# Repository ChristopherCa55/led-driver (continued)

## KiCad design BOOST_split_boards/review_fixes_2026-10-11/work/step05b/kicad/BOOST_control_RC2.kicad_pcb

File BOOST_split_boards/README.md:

# BOOST LED driver — two-board split, routed (KiCad 10)

## Current state (2026-09-25): start here

**The release package is `FINAL_2026-09-25/`** (scenario A: 5 bare PCBs of each board, 2 complete sets assembled
by JLCPCB). Start with `FINAL_2026-09-25/README.md` and its `7_docs/ORDER_CHECKLIST.md`.

**Schematic rev6 is in `BOOST-github/BOOST/BOOST.kicad_sch`** (written 2026-09-25 on the user's OK).
- Rev5 is backed up in `previous/2026-09-25/schematic_rev5/`.
- ERC 0/0, the same report as rev5; netlist `BOOST_9-25_rev6.net`.
- Netdiff: six values only. Parity 0 on both boards. DRC 0 errors, 0 unconnected.
- Nothing is open before ordering; follow `fab_2026-09-24/ORDER_CHECKLIST.md`.

The re-designed boards are not the `BOOST_power.kicad_pcb` / `BOOST_control.kicad_pcb` in this folder. Those are the
older routing described below, kept as shipped. The current boards (working copies keep `_NOT_FOR_FAB`; the release
copies are in `FINAL_2026-09-25/2_boards/`):

| | Board | Status |
|---|---|---|
| Power | `route_2026-09-16/BOOST_power_route_v19_NOT_FOR_FAB.kicad_pcb` | **release (RC2)**: v18 + rev6 values |
| Power | `route_2026-09-16/BOOST_power_route_v18_NOT_FOR_FAB.kicad_pcb` | v17 + via moves + J10 1.05 mm (approved 2026-09-24) |
| Power | `route_2026-09-16/BOOST_power_route_v17_NOT_FOR_FAB.kicad_pcb` | frozen v16 + MOSFET orientation silk |
| Card | `card_route_2026-09-22/BOOST_control_route_c3b_NOT_FOR_FAB.kicad_pcb` | **release (RC2)**: c3 + J11 1.05 mm |
| Card | `card_route_2026-09-22/BOOST_control_route_c3_NOT_FOR_FAB.kicad_pcb` | accepted 2026-09-24 |

- Fabrication + assembly package: `fab_2026-09-24/README.md` (RC2), `COST_SUMMARY.md`, `ORDER_CHECKLIST.md`.
- Assembly pack: `BUILD_NOTES.md` and `case_drilling_2026-09-15/` (rev B).
- 3D model and clearances: `assembly_3d_2026-09-24/` (rebuilt 2026-09-25 with the chosen hardware).
- M1 turn-off re-check with the routed loop: `sim_m1_2026-09-24/README.md` (accepted 2026-09-25).
- `BOOST_power.kicad_pro` carries netclass priorities (2026-09-24; backup in `previous/2026-09-24/`).

The rest of this file describes the older routing and is kept for reference.

| file | what |
|---|---|
| `BOOST_power.kicad_pcb` + `.kicad_pro` | 74 × 86 mm, 8 layers, 121 footprints |
| `BOOST_control.kicad_pcb` + `.kicad_pro` | 60 × 60 mm, 8 layers, 154 footprints |
| `DRC_power.rpt`, `DRC_control.rpt` | KiCad 10 DRC, run on these exact files |
| `power_routed.png`, `control_routed.png` | layer-coloured plots |
| `previous/` | the boards as they were before this pass |

Keep the `.kicad_pro` beside each board — it carries the net classes, and without
it DRC falls back to defaults and reports differently.

## Final state, measured by KiCad 10 DRC on the delivered files

| | POWER | CONTROL |
|---|---|---|
| unconnected **pads** | **0** | **0** |
| unconnected items (zone fill) | 2 | **0** |
| clearance | **0** | **0** |
| shorting items | **0** | **0** |
| hole-to-hole / hole clearance | **0** | **0** |
| solder-mask bridges | **0** | **0** |
| silkscreen | **0** | **0** |
| isolated copper | **0** | **0** |
| dangling track/via | 1 | **0** |
| library warning | 1 | 0 |
| track segments / vias / zones | 4630 / 305 / 16 | 3061 / 357 / 4 |

Every pad-to-pad connection on both boards is routed. The two remaining items on
the power board are between two *zones* — a fragment of the F.Cu ground pour that
does not reach the B.Cu ground pour across the surface. Both boards keep solid
ground planes on In1 and In6 with hundreds of stitching vias, so those fragments
are grounded through the stack; the ratsnest line is KiCad noting that no surface
copper joins them directly.

The `lib_footprint_issues` warning says the footprint library `CSCF3218-6R8MC`
(the inductor L1) is not in your footprint library table. The footprint itself is
embedded in the board and is correct — this is about your library configuration,
not the layout, and it goes away once that library is registered.

## Stackup (8 layers, both boards)

```
F.Cu    components, signal, high-current pours (2 oz)
In1.Cu  solid GND plane        <- no tracks, verified 0
In2.Cu  signal
In3.Cu  signal
In4.Cu  5V plane + signal
In5.Cu  signal
In6.Cu  solid GND plane        <- no tracks, verified 0
B.Cu    components, gate drive, signal (2 oz)
```

## Net classes (in the .kicad_pro, enforced by DRC)

| class | track | clearance | via | nets |
|---|---|---|---|---|
| Power | 2.0 mm | 0.25 mm | 0.8/0.4 | Vin, rsense_lo, LX, m2/3/4_source, Vout_1/2/3, Output1/2/3_drain, GND |
| Gate | 0.5 mm | 0.20 mm | 0.6/0.3 | GATE_M1…M7 |
| Rail | 0.8 mm | 0.20 mm | 0.6/0.3 | 12V, 5V, analog_5V |
| Default | 0.15 mm | 0.15 mm | 0.45/0.25 | everything else |

## High-current copper — measured, not assumed

The check erodes each net's copper by a disc and asks whether its power pads are
still joined; the largest disc that survives is the narrowest continuous path
between them. Only pads at least 1.5 mm across count as power terminals — an
0805 bypass cap taps the rail, it does not carry the rail current. Compared
against IPC-2221, 2 oz external, 30 °C rise.

```
net              A rms    need   narrowest continuous path
m3_source         12.0    2.37mm     2.99 mm   ok
Vout_1             3.3    0.40mm     0.45 mm   ok
Vout_3             2.7    0.30mm     0.45 mm   ok
Output1_drain      2.6    0.29mm     0.45 mm   ok
Output2_drain      2.6    0.29mm     0.45 mm   ok
Output3_drain      2.6    0.29mm     0.45 mm   ok
12V                0.5    0.03mm     0.40 mm   ok
5V                 0.3    0.01mm     0.20 mm   ok
analog_5V          0.1    0.00mm     0.45 mm   ok

Vin               20.7    5.04mm     4.59 mm   91% of requirement
m2_source         12.0    2.37mm     2.04 mm   86%
m4_source         12.0    2.37mm     1.59 mm   67%
Vout_2             3.7    0.47mm     0.40 mm   85%
rsense_lo         20.7    5.04mm     0.45 mm   path crosses a via
LX                20.7    5.04mm     0.45 mm   path crosses a via
GND               20.7    5.04mm     0.40 mm   path crosses a via
```

Read the last three carefully. 0.45 mm is a via barrel: the single best path
between those power terminals goes through one via. The measure follows one path
and does not add up parallel ones, so real capacity is higher — GND in particular
has two solid inner planes and hundreds of stitching vias. But for rsense_lo and
LX at 20.7 A it is a real finding, and the cause is placement: R1 (the 2 mΩ
shunt), L1 and the TO-220 drains sit far enough apart that no single-layer pour
can join them at 5 mm. Two ways to close it, both needing a change you asked me
not to make on my own:

* move R1, L1 and M1/M5/M6/M7 into one cluster so a single F.Cu pour spans them —
  which is what a 20 A switching loop wants anyway; or
* keep the placement and add deliberate via arrays (15–20 barrels in parallel) at
  each F.Cu-to-B.Cu crossing on Vin, rsense_lo and LX.

## Design changes made in this pass

1. **All routing rebuilt, escape vias first.** The old boards left ~37 pads that
   nothing could reach; mapping the copper around them showed the same cause
   every time — by the time the router got there, no legal via site was left near
   the pad. Giving every signal pad its own escape via while the board was still
   empty (368 of them, 100% placed) removed that class of failure outright.
2. **High-current pours rebuilt as non-overlapping regions.** The twelve pours
   were convex hulls totalling 9300 mm² on a 6170 mm² board, so zone priority
   carved most of them away: rsense_lo was filling 3% of its own outline,
   m3_source 1.9%. Each net now grows outward from its own pads and stops where
   it meets another, so the regions tile instead of fighting. rsense_lo went from
   15.6 mm² of copper to 212 mm², Vout_1 from 56 mm² to 442 mm².
3. **Two ineffective rail pours dropped.** On In4 the 5V zone outranked 12V and
   analog_5V, which were left filling 1.0 mm² and 5.0 mm² — stranded rings around
   their own pads that showed up as unconnected zones. Those two rails now route
   as 0.8 mm tracks, about 25× what 0.5 A and 0.1 A need.
4. **Zone fill parameters set to the net class.** Local clearance was 0.3 mm
   where the class asks 0.25 mm, and the extra 0.05 mm a side stopped the fill
   squeezing past tracks, stranding pours around pads. DRC still enforces
   0.25 mm.
5. **D19 moved onto the board.** The TVS was at x = 119 mm with the board ending
   at x = 104 — 15 mm off the edge, so its LX and GND pins could never be
   reached. It now sits at (83.0, 49.8) on the underside, the nearest free spot
   clearing every courtyard, mounting hole and silkscreen. **This one wants your
   eye**: it ended up 25 mm from the switching node, and a TVS belongs close to
   what it protects. If you can free space near L1/M1, move it there.
6. **Denser ground stitching**, and stitching vias driven into pour islands that
   held a pad but no via.

Board outline, layer count, stackup, schematic, netlist, footprints and every
other component's position are unchanged.

## What I did not do

No DRC rule was disabled, no violation was marked as an exclusion, and no net
class was weakened. Nothing above is hidden — the two zone items and the one
dangling stub are in `DRC_power.rpt` with coordinates.

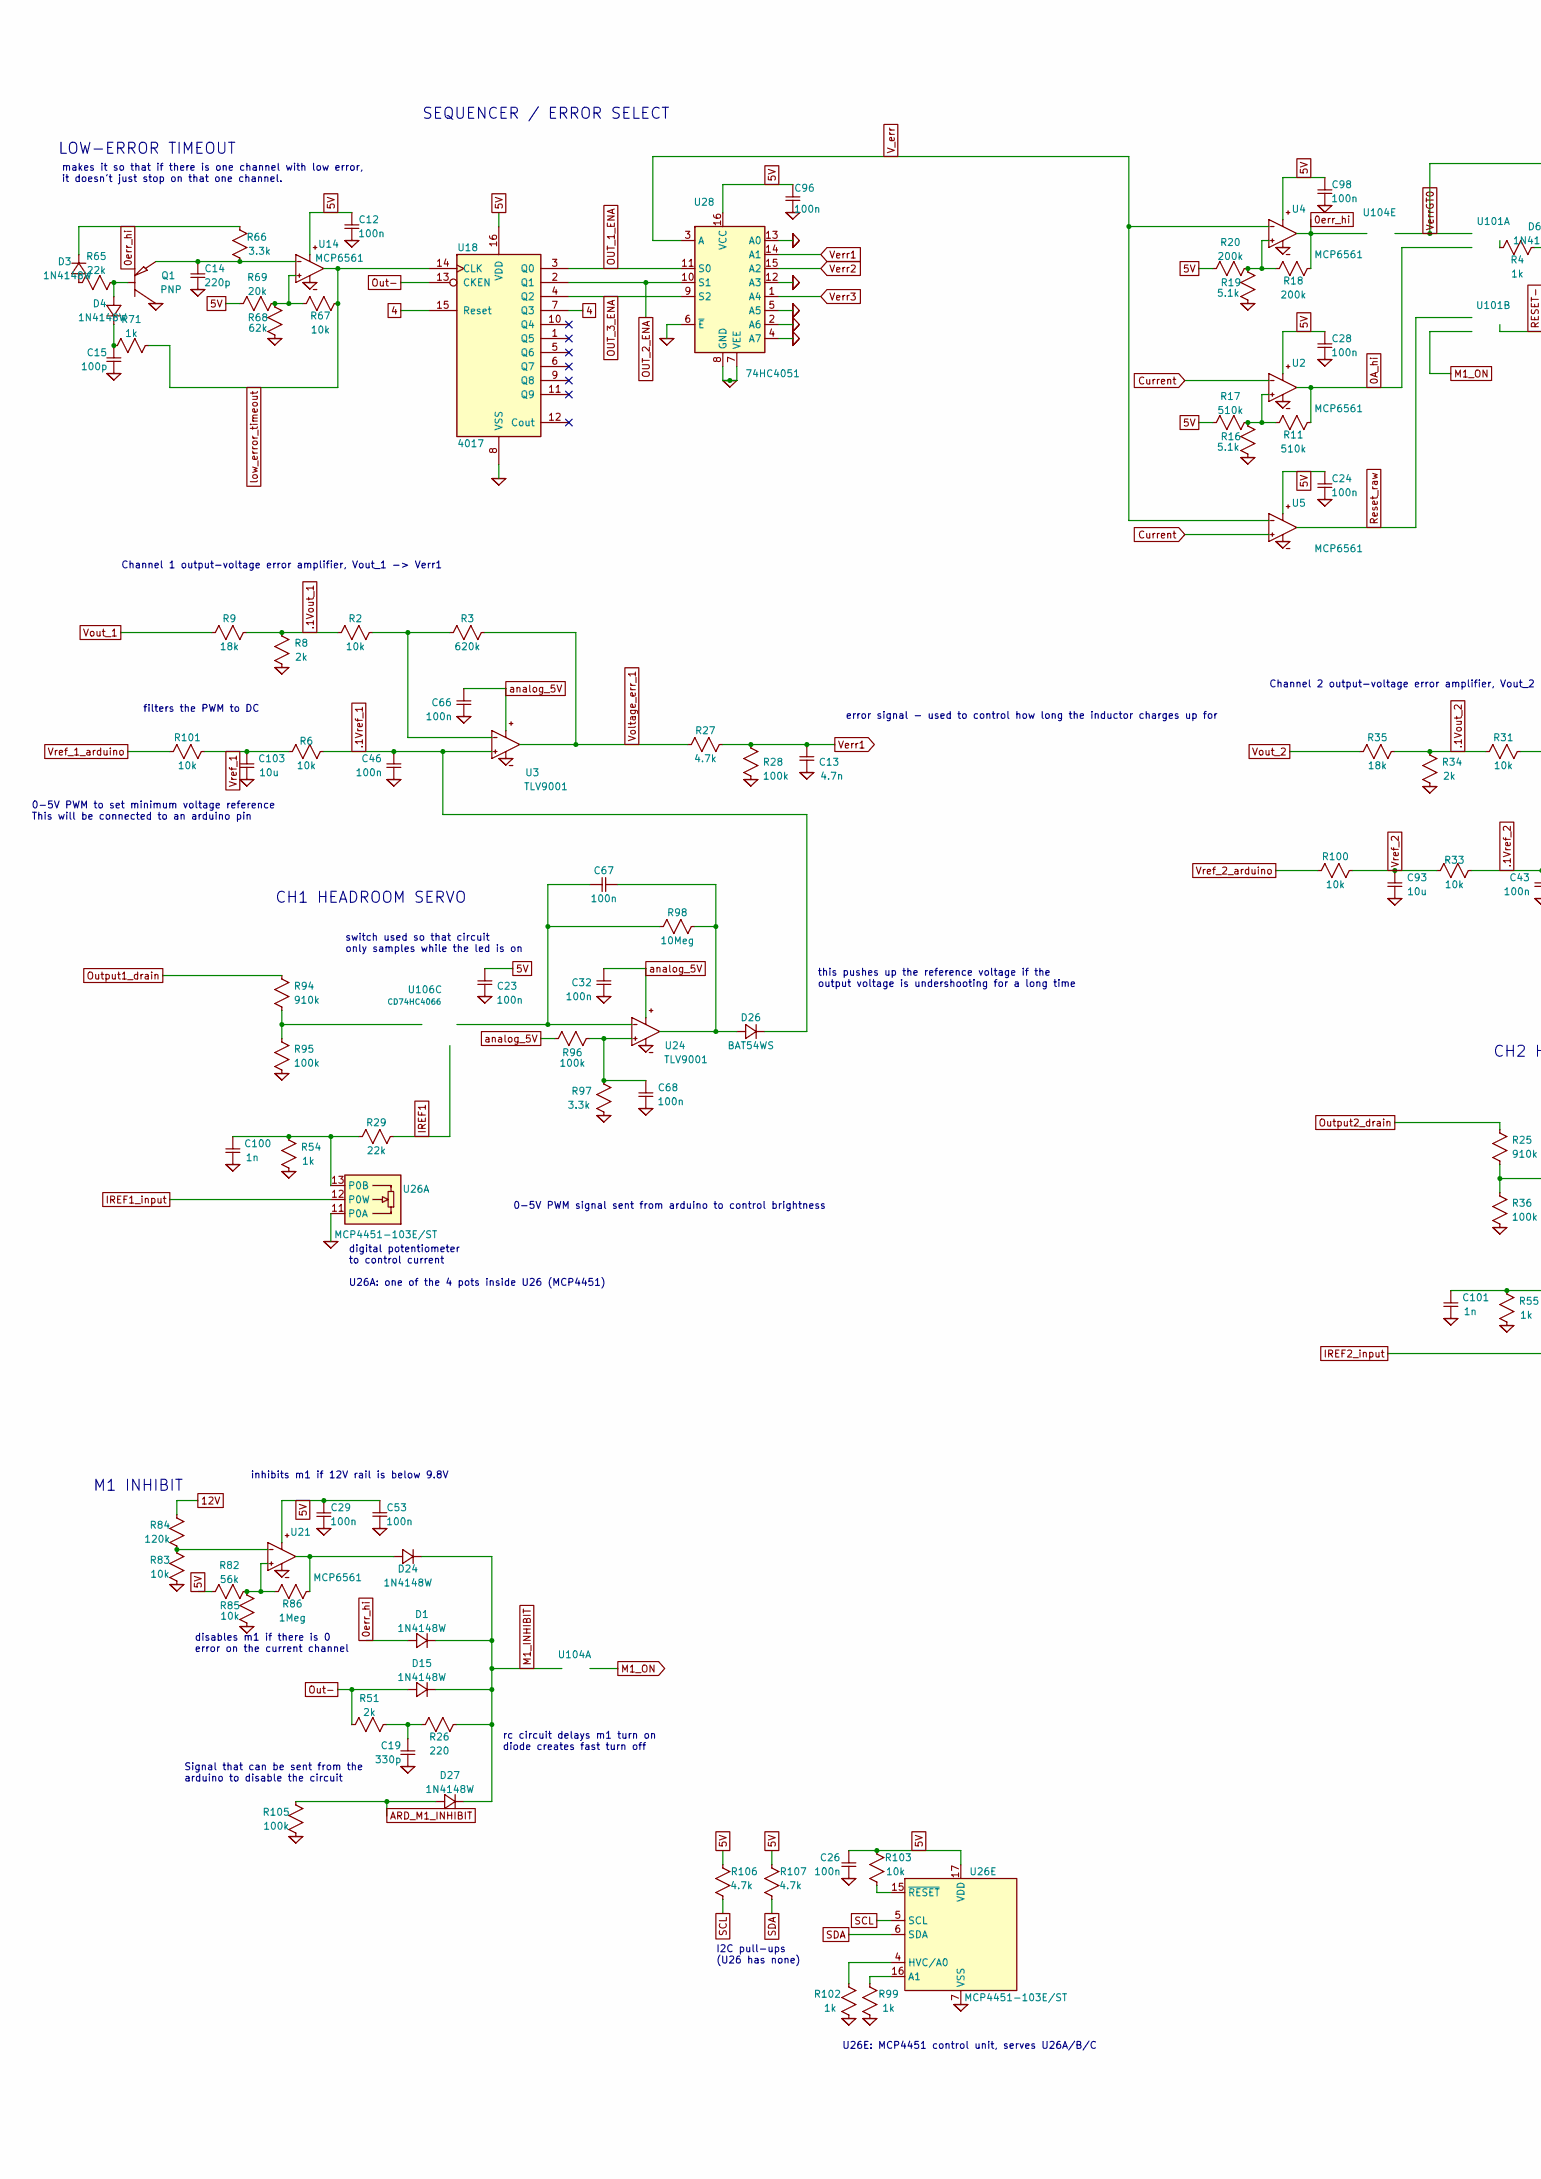
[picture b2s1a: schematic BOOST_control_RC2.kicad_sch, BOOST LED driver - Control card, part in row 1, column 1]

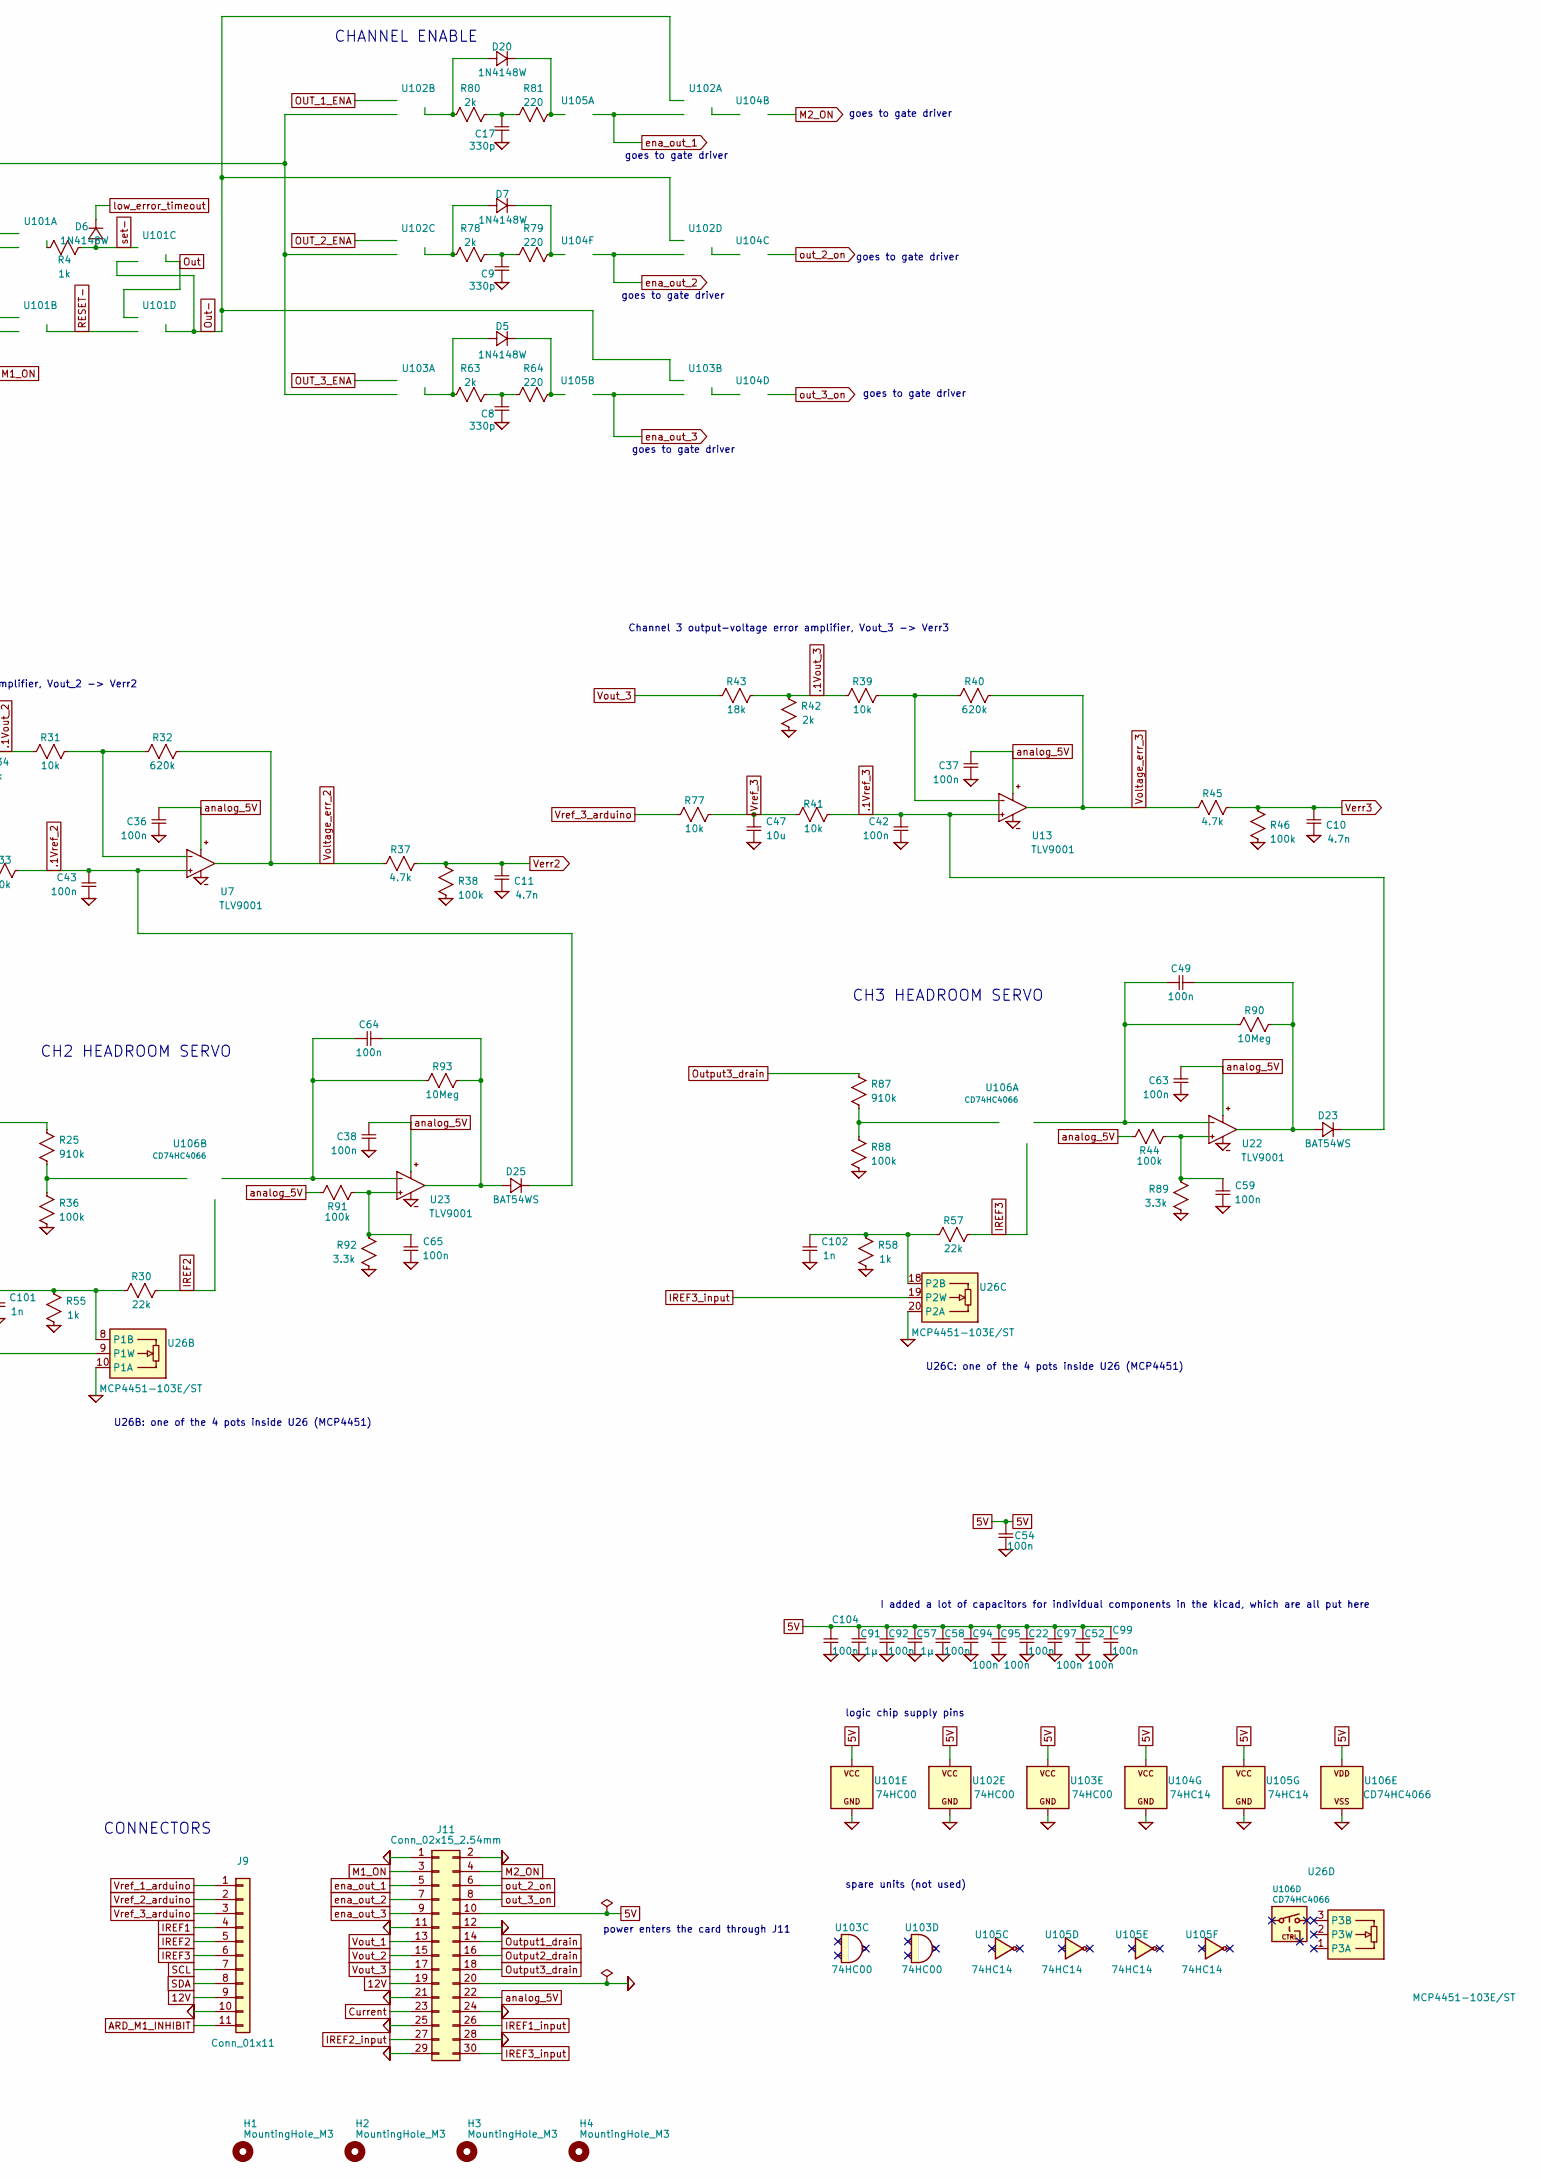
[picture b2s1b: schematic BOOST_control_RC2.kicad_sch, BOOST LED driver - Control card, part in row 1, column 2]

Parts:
C8, C9, C17, C19: 330p; C_0603_1608Metric
C10, C11, C13: 4.7n; C_0603_1608Metric
C12, C22, C23, C24, C26, C28, C29, C32, C36, C37, C38, C42, C43, C46, C52, C53, C54, C58, C59, C63, C65, C66, C68, C92, C94, C95, C96, C97, C98, C99, C104: 100n; C_0603_1608Metric
C14: 220p; C_0603_1608Metric
C15: 100p; C_0603_1608Metric
C47, C93, C103: 10u; C_0603_1608Metric
C49, C64, C67: 100n; C_1206_3216Metric
C57, C91: 1µ; C_0805_2012Metric
C100, C101, C102: 1n; C_0603_1608Metric
D1, D3, D4, D5, D6, D7, D15, D20, D24, D27: 1N4148W; D_SOD-123
D23, D25, D26: BAT54WS; D_SOD-323
H1, H2, H3, H4: MountingHole_M3; MountingHole_3.2mm_M3
J9: Conn_01x11; WirePads_11_Staggered_P1.27mm_Drill1.0mm_TieSlots
J11: Conn_02x15_2.54mm; PinHeader_2x15_P2.54mm_Vertical; MPN TSW-115-07-G-D
Q1: PNP; SOT-23
R2, R6, R31, R33, R39, R41, R67, R77, R83, R85, R100, R101, R103: 10k; R_0603_1608Metric
R3, R32, R40: 620k; R_0603_1608Metric
R4, R54, R55, R58, R71, R99, R102: 1k; R_0603_1608Metric
R8, R34, R42, R51, R63, R78, R80: 2k; R_0603_1608Metric
R9, R35, R43: 18k; R_0805_2012Metric
R11, R17: 510k; R_0603_1608Metric
R16, R19: 5.1k; R_0603_1608Metric
R18, R20: 200k; R_0603_1608Metric
R25, R87, R94: 910k; R_0805_2012Metric
R26, R64, R79, R81: 220; R_0603_1608Metric
R27, R37, R45: 4.7k; R_0603_1608Metric
R28, R36, R38, R44, R46, R88, R91, R95, R96, R105: 100k; R_0603_1608Metric
R29, R30, R57: 22k; R_0805_2012Metric
R65: 22k; R_0603_1608Metric
R66, R89, R92, R97: 3.3k; R_0603_1608Metric
R68: 62k; R_0603_1608Metric
R69: 20k; R_0603_1608Metric
R82: 56k; R_0603_1608Metric
R84: 120k; R_0603_1608Metric
R86: 1Meg; R_0805_2012Metric
R90, R93, R98: 10Meg; R_0603_1608Metric
R106, R107: 4.7k; R_0402_1005Metric
U2, U4, U5, U14, U21: MCP6561; SOT-23-5
U3, U7, U13, U22, U23, U24: TLV9001; SOT-23-5; MPN TLV9001IDBVR
U18: 4017; SOIC-16_3.9x9.9mm_P1.27mm
U26: MCP4451-103E/ST; TSSOP-20_4.4x6.5mm_P0.65mm; MPN MCP4451-103E/ST; LCSC C145613
U28: 74HC4051; SOIC-16_3.9x9.9mm_P1.27mm
U101, U102, U103: 74HC00; SOIC-14_3.9x8.7mm_P1.27mm
U104, U105: 74HC14; SOIC-14_3.9x8.7mm_P1.27mm
U106: CD74HC4066; SOIC-14_3.9x8.7mm_P1.27mm

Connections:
0A_hi: R11.1, U2.1 (OUT), U101.2 (B)
0err_hi: D1.2 (+), D3.1 (-), R18.1, R66.1, U4.1 (OUT), U104.11 (A)
4: U18.7 (Q3), U18.15 (Reset)
5V: C12.1, C22.1, C23.1, C24.1, C26.1, C28.1, C29.1, C52.1, C53.2, C54.1, C57.2, C58.1, C91.2, C92.1, C94.1, C95.1, C96.1, C97.1, C98.1, C99.1, C104.1, J11.10, R17.2, R20.2, R69.2, R82.1, R103.1, R106.1, R107.1, U2.5 (V+), U4.5 (V+), U5.5 (V+), U14.5 (V+), U18.16 (VDD), U21.5 (V+), U26.17 (VDD), U28.16 (VCC), U101.14 (VCC), U102.14 (VCC), U103.14 (VCC), U104.14 (VCC), U105.14 (VCC), U106.14 (VDD)
12V: J9.9, J11.19, R84.1
.1Vout_1: R2.2, R8.1, R9.1
.1Vout_2: R31.2, R34.1, R35.1
.1Vout_3: R39.2, R42.1, R43.1
.1Vref_1: C46.1, D26.1 (-), R6.2, U3.3 (In+)
.1Vref_2: C43.1, D25.1 (-), R33.2, U7.3 (In+)
.1Vref_3: C42.1, D23.1 (-), R41.2, U13.3 (In+)
ARD_M1_INHIBIT: D27.2 (+), J9.11, R105.1
Current: J11.23, U2.4 (In-), U5.3 (In+)
GND: C8.1, C9.1, C10.1, C11.1, C12.2, C13.1, C14.2, C15.2, C17.1, C19.2, C22.2, C23.2, C24.2, C26.2, C28.2, C29.2, C32.2, C36.1, C37.1, C38.1, C42.2, C43.2, C46.2, C47.2, C52.2, C53.1, C54.2, C57.1, C58.2, C59.2, C63.2, C65.2, C66.2, C68.2, C91.1, C92.2, C93.2, C94.2, C95.2, C96.2, C97.2, C98.2, C99.2, C100.2, C101.2, C102.2, C103.2, C104.2, J9.10, J11.1, J11.2, J11.11, J11.12, J11.20, J11.21, J11.24, J11.25, J11.28, J11.29, Q1.3 (C), R8.2, R16.2, R19.2, R28.1, R34.2, R36.2, R38.1, R42.2, R46.1, R54.2, R55.2, R58.2, R68.2, R83.2, R85.2, R88.2, R89.2, R92.2, R95.2, R97.2, R99.2, R102.2, R105.2, U2.2 (V-), U3.2 (V-), U4.2 (V-), U5.2 (V-), U7.2 (V-), U13.2 (V-), U14.2 (V-), U18.8 (VSS), U21.2 (V-), U22.2 (V-), U23.2 (V-), U24.2 (V-), U26.7 (VSS), U26.10 (P1A), U26.11 (P0A), U26.20 (P2A), U28.2 (A6), U28.4 (A7), U28.5 (A5), U28.6 (~E), U28.7 (VEE), U28.8 (GND), U28.12 (A3), U28.13 (A0), U101.7 (GND), U102.7 (GND), U103.7 (GND), U104.7 (GND), U105.7 (GND), U106.7 (VSS)
IREF1: J9.4, R29.1, U106.6 (CTRL)
IREF1_input: J11.26, U26.12 (P0W)
IREF2: J9.5, R30.1, U106.5 (CTRL)
IREF2_input: J11.27, U26.9 (P1W)
IREF3: J9.6, R57.1, U106.13 (CTRL)
IREF3_input: J11.30, U26.19 (P2W)
M1_INHIBIT: D1.1 (-), D15.1 (-), D24.1 (-), D27.1 (-), R26.1, U104.1 (A)
M1_ON: J11.3, U101.5 (B), U104.2 (Y)
M2_ON: J11.4, U104.4 (Y)
unnamed: C8.2, R63.1, R64.1
unnamed: C9.2, R78.1, R79.1
unnamed: C17.2, R80.1, R81.1
unnamed: C19.1, R26.2, R51.2
unnamed: D3.2 (+), R65.2
unnamed: D4.2 (+), Q1.1 (B), R65.1
unnamed: C15.1, D4.1 (-), R71.1
unnamed: D5.2 (+), R63.2, U103.3 (Y)
unnamed: D5.1 (-), R64.2, U105.3 (A)
unnamed: D7.2 (+), R78.2, U102.8 (Y)
unnamed: D7.1 (-), R79.2, U104.13 (A)
unnamed: D20.2 (+), R80.2, U102.6 (Y)
unnamed: D20.1 (-), R81.2, U105.1 (A)
unnamed: C49.2, D23.2 (+), R90.2, U22.1 (OUT)
unnamed: D24.2 (+), R86.1, U21.1 (OUT)
unnamed: C64.2, D25.2 (+), R93.2, U23.1 (OUT)
unnamed: C67.2, D26.2 (+), R98.2, U24.1 (OUT)
unnamed: C14.1, Q1.2 (E), R66.2, U14.4 (In-)
unnamed: R11.2, R16.1, R17.1, U2.3 (In+)
unnamed: R2.1, R3.2, U3.4 (In-)
unnamed: R18.2, R19.1, R20.1, U4.3 (In+)
unnamed: R31.1, R32.2, U7.4 (In-)
unnamed: R39.1, R40.2, U13.4 (In-)
unnamed: R67.2, R68.1, R69.1, U14.3 (In+)
unnamed: R82.2, R85.1, R86.2, U21.3 (In+)
unnamed: R83.1, R84.2, U21.4 (In-)
unnamed: C59.1, R44.2, R89.1, U22.3 (In+)
unnamed: C65.1, R91.2, R92.1, U23.3 (In+)
unnamed: C68.1, R96.2, R97.1, U24.3 (In+)
unnamed: C100.1, R29.2, R54.1, U26.13 (P0B)
unnamed: C101.1, R30.2, R55.1, U26.8 (P1B)
unnamed: C102.1, R57.2, R58.1, U26.18 (P2B)
unnamed: R99.1, U26.16 (A1)
unnamed: R102.1, U26.4 (HVC/A0)
unnamed: R103.2, U26.15 (~RESET)
unnamed: R4.2, U101.3 (Y)
unnamed: U102.3 (Y), U104.3 (A)
unnamed: U102.11 (Y), U104.5 (A)
unnamed: U103.6 (Y), U104.9 (A)
unnamed: R87.2, R88.1, U106.1 (A)
unnamed: C49.1, R90.1, U22.4 (In-), U106.2 (B)
unnamed: R25.2, R36.1, U106.3 (A)
unnamed: C64.1, R93.1, U23.4 (In-), U106.4 (B)
unnamed: R94.2, R95.1, U106.8 (A)
unnamed: C67.1, R98.1, U24.4 (In-), U106.9 (B)
OUT_1_ENA: U18.3 (Q0), U28.11 (S0), U102.4 (A)
OUT_2_ENA: U18.2 (Q1), U28.10 (S1), U102.10 (A)
OUT_3_ENA: U18.4 (Q2), U28.9 (S2), U103.1 (A)
Out: U101.8 (Y), U101.13 (A)
Out-: D15.2 (+), R51.1, U18.13 (CKEN), U101.9 (B), U101.11 (Y), U102.1 (A), U102.13 (A), U103.5 (B)
Output1_drain: J11.14, R94.1
Output2_drain: J11.16, R25.1
Output3_drain: J11.18, R87.1
RESET-: U101.6 (Y), U101.12 (B)
Reset_raw: U5.1 (OUT), U101.4 (A)
SCL: J9.7, R106.2, U26.5 (SCL)
SDA: J9.8, R107.2, U26.6 (SDA)
V_err: U4.4 (In-), U5.4 (In-), U28.3 (A)
Verr1: C13.2, R27.2, R28.2, U28.14 (A1)
Verr2: C11.2, R37.2, R38.2, U28.15 (A2)
Verr3: C10.2, R45.2, R46.2, U28.1 (A4)
VerrGT0: U101.1 (A), U102.5 (B), U102.9 (B), U103.2 (B), U104.10 (Y)
Voltage_err_1: R3.1, R27.1, U3.1 (OUT)
Voltage_err_2: R32.1, R37.1, U7.1 (OUT)
Voltage_err_3: R40.1, R45.1, U13.1 (OUT)
Vout_1: J11.13, R9.2
Vout_2: J11.15, R35.2
Vout_3: J11.17, R43.2
Vref_1: C103.1, R6.1, R101.2
Vref_1_arduino: J9.1, R101.1
Vref_2: C93.1, R33.1, R100.2
Vref_2_arduino: J9.2, R100.1
Vref_3: C47.1, R41.1, R77.2
Vref_3_arduino: J9.3, R77.1
analog_5V: C32.1, C36.2, C37.2, C38.2, C63.1, C66.1, J11.22, R44.1, R91.1, R96.1, U3.5 (V+), U7.5 (V+), U13.5 (V+), U22.5 (V+), U23.5 (V+), U24.5 (V+)
ena_out_1: J11.5, U102.2 (B), U105.2 (Y)
ena_out_2: J11.7, U102.12 (B), U104.12 (Y)
ena_out_3: J11.9, U103.4 (A), U105.4 (Y)
low_error_timeout: D6.1 (-), R67.1, R71.2, U14.1 (OUT), U18.14 (CLK)
out_2_on: J11.6, U104.6 (Y)
out_3_on: J11.8, U104.8 (Y)
set-: D6.2 (+), R4.1, U101.10 (A)

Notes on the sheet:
M1 INHIBIT
disables m1 if there is 0 error on the current channel
goes to gate driver
CONNECTORS
U26B: one of the 4 pots inside U26 (MCP4451)
U26A: one of the 4 pots inside U26 (MCP4451)
switch used so that circuit only samples while the led is on
0-5V PWM to set minimum voltage reference This will be connected to an arduino pin
U26C: one of the 4 pots inside U26 (MCP4451)
spare units (not used)
this pushes up the reference voltage if the output voltage is undershooting for a long time
LOW-ERROR TIMEOUT
0-5V PWM signal sent from arduino to control brightness
Channel 2 output-voltage error amplifier, Vout_2 -> Verr2
logic chip supply pins
power enters the card through J11
Signal that can be sent from the arduino to disable the circuit
CH3 HEADROOM SERVO
rc circuit delays m1 turn on diode creates fast turn off
inhibits m1 if 12V rail is below 9.8V
CH1 HEADROOM SERVO
filters the PWM to DC
CH2 HEADROOM SERVO
I added a lot of capacitors for individual components in the kicad, which are all put here
U26E: MCP4451 control unit, serves U26A/B/C
digital potentiometer to control current
Channel 1 output-voltage error amplifier, Vout_1 -> Verr1
SEQUENCER / ERROR SELECT
error signal - used to control how long the inductor charges up for
Channel 3 output-voltage error amplifier, Vout_3 -> Verr3
CHANNEL ENABLE
makes it so that if there is one channel with low error, it doesn't just stop on that one channel.
I2C pull-ups (U26 has none)

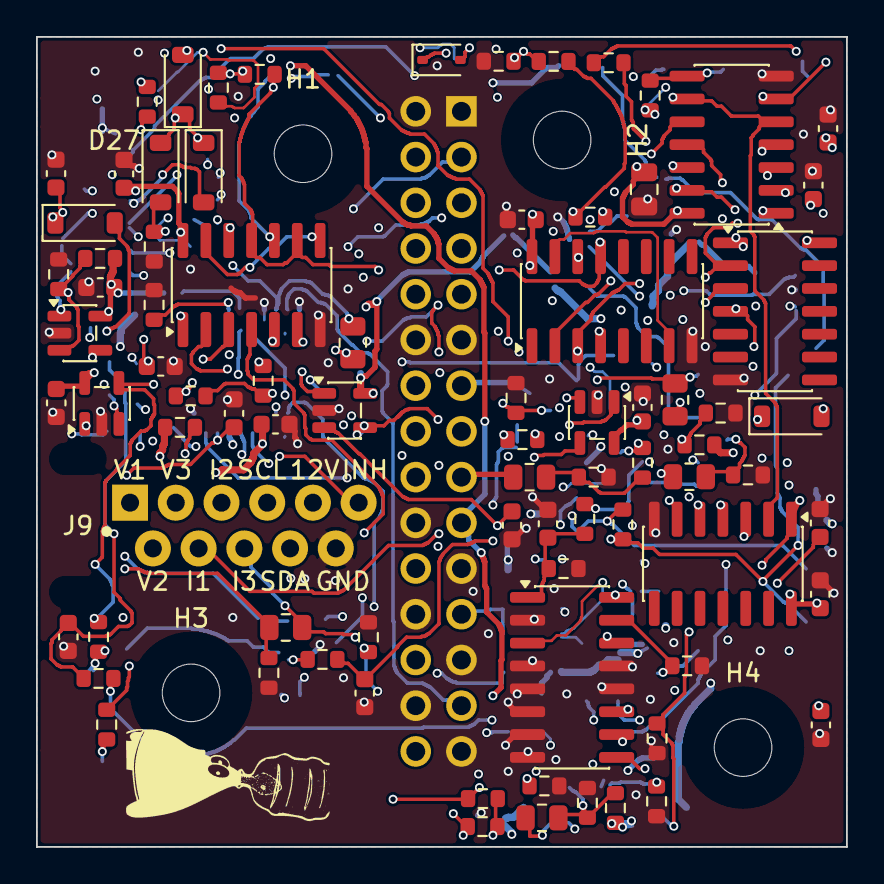
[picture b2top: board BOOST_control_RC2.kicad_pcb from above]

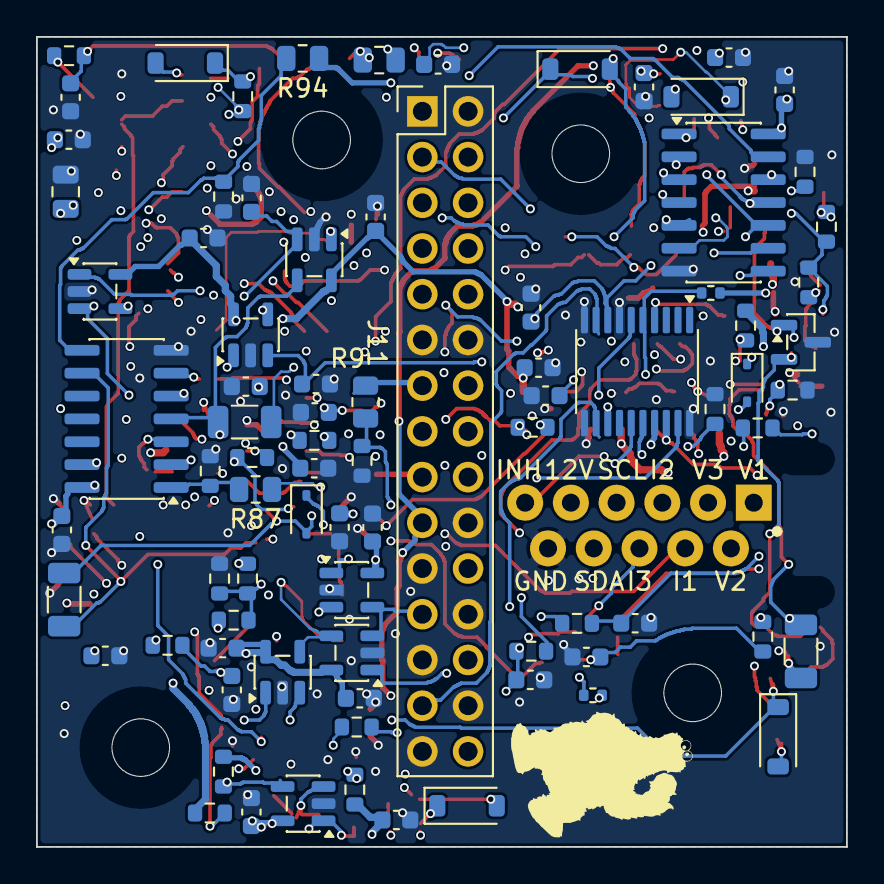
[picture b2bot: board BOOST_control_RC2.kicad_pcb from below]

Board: 6 copper layers, 45.0 x 45.0 mm, 168 parts (83 on the bottom side), 105 nets.
